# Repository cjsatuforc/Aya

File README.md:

# Aya

A general purpose TX module.

See `docs` for details/build instructions.

## Credits

  - [Deviation](http://www.deviationtx.com/) firmware

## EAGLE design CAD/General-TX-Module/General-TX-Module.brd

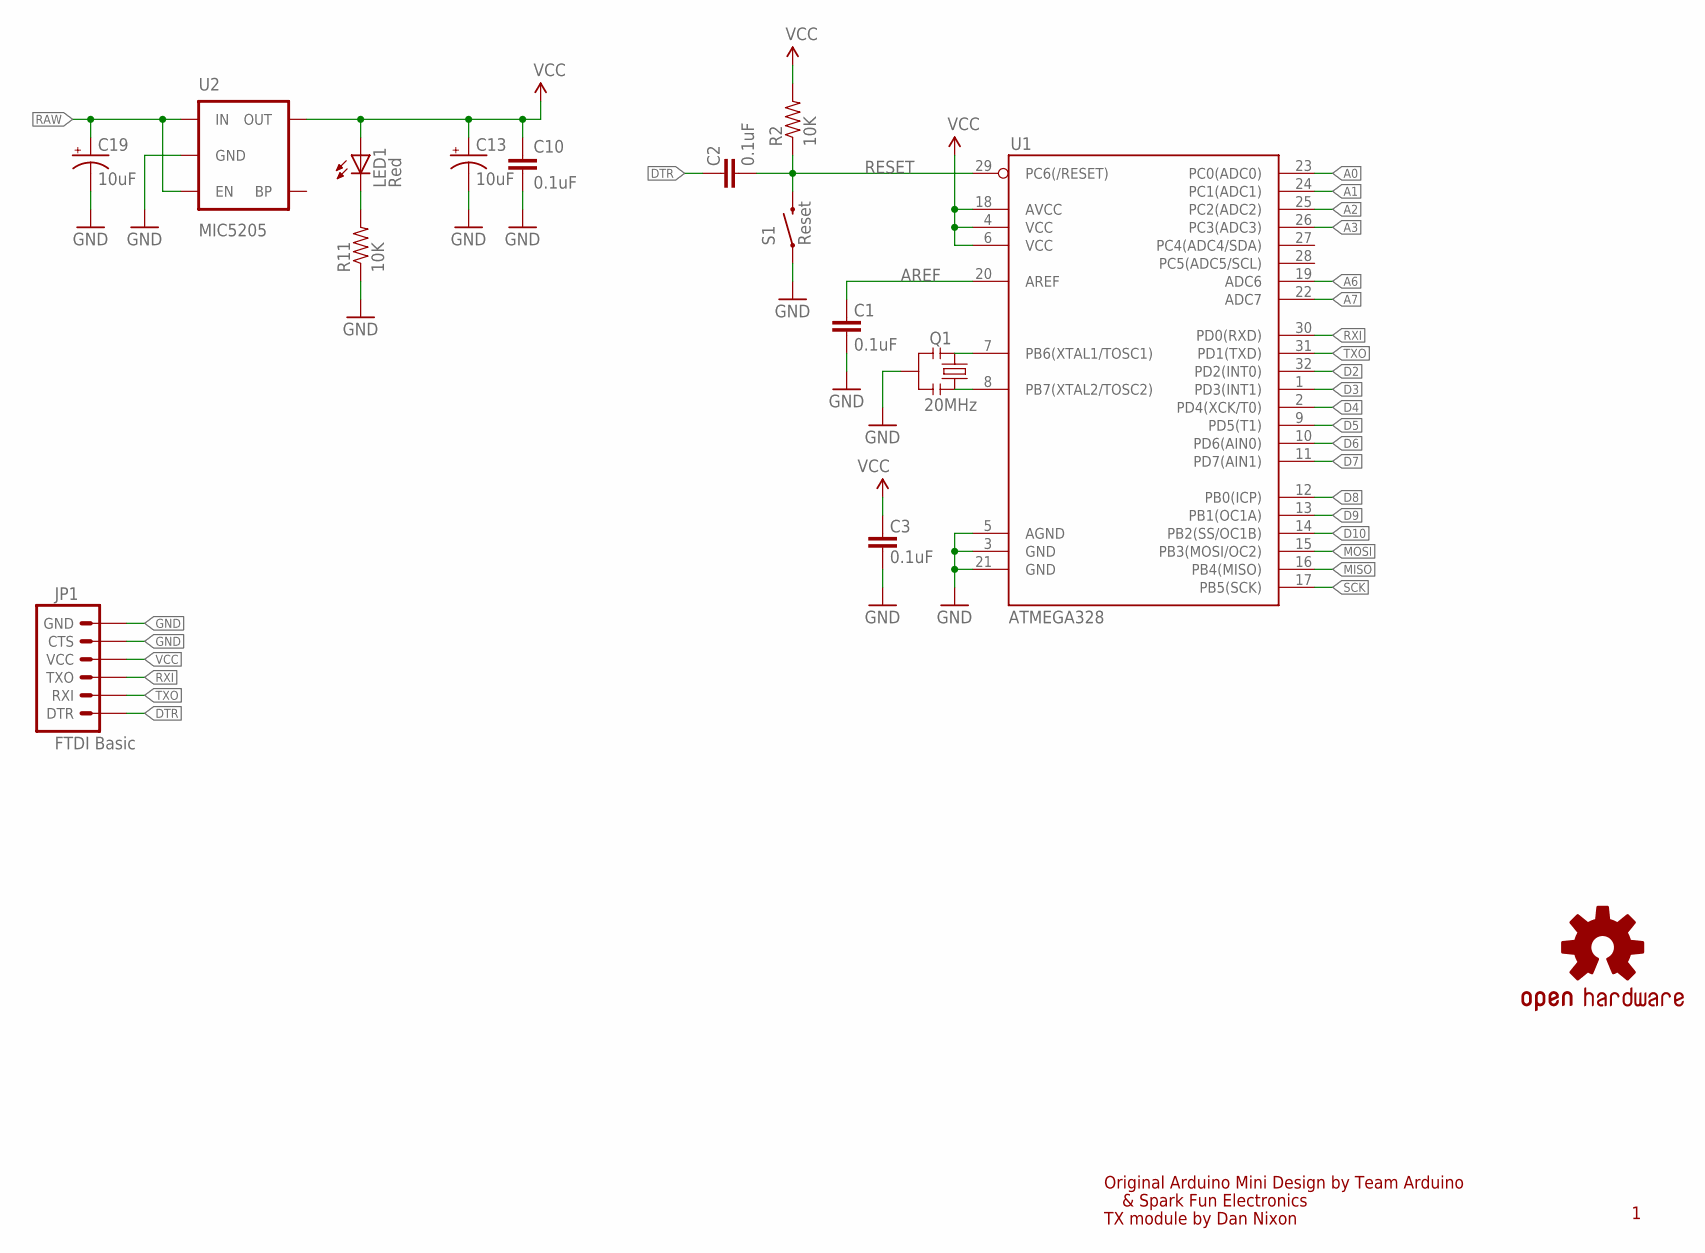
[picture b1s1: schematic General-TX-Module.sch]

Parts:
C1, C2, C3, C10: 0.1uF; 0603-CAP
C13, C19: 10uF; EIA3216
JP1: FTDI Basic; 1X06
LED1: Red; 0603-LED-ALT1
Q1: 20MHz; RESONATOR-SMD-1:1
R2, R11: 10K; 0603-RES
S1: Reset; TACTILE-SWITCH-SMD-ALT01
U1: ATMEGA328; TQFP32-08
U2: MIC5205; SOT23-5
U$3: OSHW-LOGOS; OSHW-LOGO-S

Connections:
A0: U1.23 (PC0(ADC0))
A1: U1.24 (PC1(ADC1))
A2: U1.25 (PC2(ADC2))
A3: U1.26 (PC3(ADC3))
A6: U1.19 (ADC6)
A7: U1.22 (ADC7)
AREF: C1.2, U1.20 (AREF)
D2: U1.32 (PD2(INT0))
D3: U1.1 (PD3(INT1))
D4: U1.2 (PD4(XCK/T0))
D5: U1.9 (PD5(T1))
D6: U1.10 (PD6(AIN0))
D7: U1.11 (PD7(AIN1))
D8: U1.12 (PB0(ICP))
D9: U1.13 (PB1(OC1A))
D10: U1.14 (PB2(SS/OC1B))
DTR: C2.2, JP1.1 (DTR)
GND: C1.1, C3.1, C10.2, C13.C (-), C19.C (-), JP1.5 (CTS), JP1.6 (GND), Q1.2, R11.1, S1.1, S1.2 (1), U1.3 (GND), U1.5 (AGND), U1.21 (GND), U2.2 (GND)
MISO: U1.16 (PB4(MISO))
MOSI: U1.15 (PB3(MOSI/OC2))
unnamed: Q1.3, U1.8 (PB7(XTAL2/TOSC2))
unnamed: Q1.1, U1.7 (PB6(XTAL1/TOSC1))
unnamed: LED1.C, R11.2
RAW: C19.A (+), U2.1 (IN), U2.3 (EN)
RESET: C2.1, R2.1, S1.3 (2), S1.4 (2), U1.29 (PC6(/RESET))
RXI: JP1.3 (TXO), U1.30 (PD0(RXD))
SCK: U1.17 (PB5(SCK))
TXO: JP1.2 (RXI), U1.31 (PD1(TXD))
VCC: C3.2, C10.1, C13.A (+), JP1.4 (VCC), LED1.A, R2.2, U1.4 (VCC), U1.6 (VCC), U1.18 (AVCC), U2.5 (OUT)

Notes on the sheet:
Original Arduino Mini Design by Team Arduino
& Spark Fun Electronics
TX module by Dan Nixon

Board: 2 copper layers, 15 parts (2 on the bottom side), 11 nets, no tracks yet.

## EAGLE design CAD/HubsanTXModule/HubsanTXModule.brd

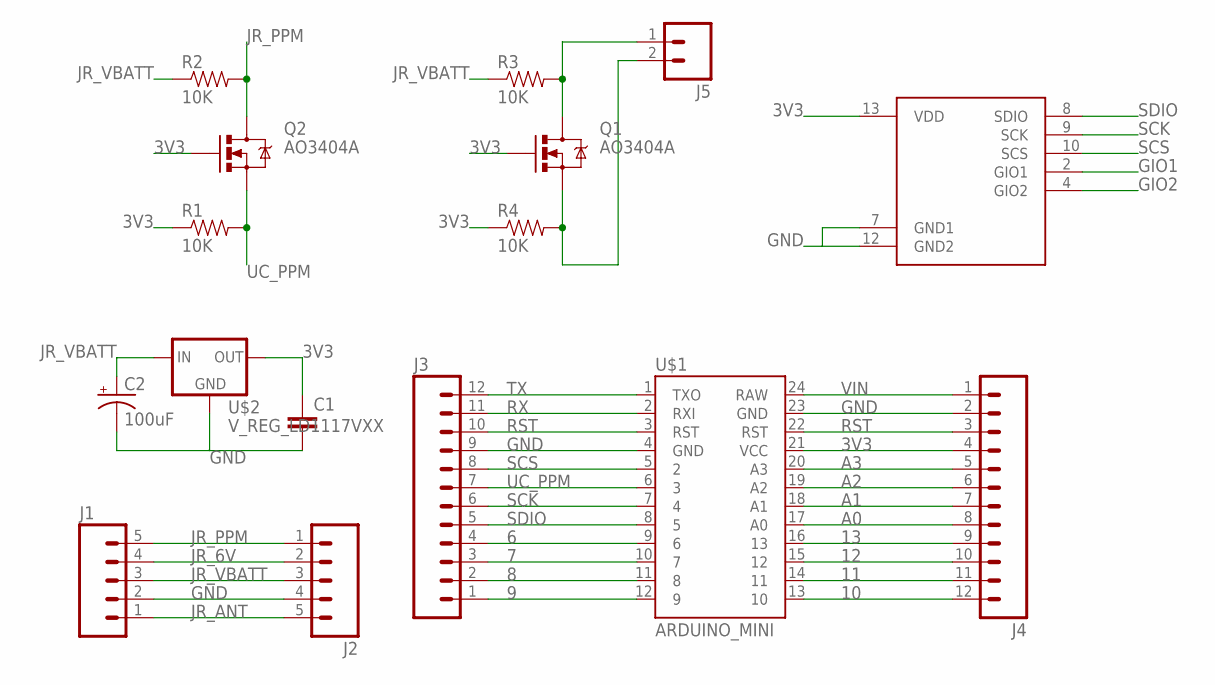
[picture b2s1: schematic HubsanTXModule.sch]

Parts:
C1: 10UF10V10%(0805); 0805-CAP
C2: 100uF; NIC_10X10.5_CAP
J1, J2: M05PTH; 1X05
J3, J4: M12PTH; 1X12
J5: M02PTH; 1X02
Q1, Q2: AO3404A; SOT23-3
R1, R2, R3, R4: 10K; 0603-RES
U$1: ARDUINO_MINI
U$2: V_REG_LD1117VXX; 78XXL
U$3: A7105_DEVBOARD; A7105_DEV1

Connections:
3V3: C1.1, J4.4, Q1.1 (G), Q2.1 (G), R1.1, R4.1, U$1.21 (VCC), U$2.GND (OUT), U$3.13 (VDD)
6: J3.4, U$1.9 (6)
7: J3.3, U$1.10 (7)
8: J3.2, U$1.11 (8)
9: J3.1, U$1.12 (9)
10: J4.12, U$1.13 (10)
11: J4.11, U$1.14 (11)
12: J4.10, U$1.15 (12)
13: J4.9, U$1.16 (13)
A0: J4.8, U$1.17 (A0)
A1: J4.7, U$1.18 (A1)
A2: J4.6, U$1.19 (A2)
A3: J4.5, U$1.20 (A3)
GIO1: U$3.2 (GIO1)
GIO2: U$3.4 (GIO2)
GND: C1.2, C2.-, J1.2, J2.4, J3.9, J4.2, U$1.4 (GND), U$1.23 (GND), U$2.IN (GND), U$3.7 (GND1), U$3.12 (GND2)
JR_6V: J1.4, J2.2
JR_ANT: J1.1, J2.5
JR_PPM: J1.5, J2.1, Q2.3 (D), R2.2
JR_VBATT: C2.+, J1.3, J2.3, R2.1, R3.1, U$2.OUT (IN)
unnamed: J5.2, Q1.2 (S), R4.2
unnamed: J5.1, Q1.3 (D), R3.2
RST: J3.10, J4.3, U$1.3 (RST), U$1.22 (RST)
RX: J3.11, U$1.2 (RXI)
SCK: J3.6, U$1.7 (4), U$3.9 (SCK)
SCS: J3.8, U$1.5 (2), U$3.10 (SCS)
SDIO: J3.5, U$1.8 (5), U$3.8 (SDIO)
TX: J3.12, U$1.1 (TXO)
UC_PPM: J3.7, Q2.2 (S), R1.2, U$1.6 (3)
VIN: J4.1, U$1.24 (RAW)

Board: 2 copper layers, 16 parts (0 on the bottom side), 28 nets, no tracks yet.

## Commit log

2016-01-08 CPPM code
2016-01-10 Add clang format
2016-01-12 Set pulse polarity
2016-01-20 Get working
2016-01-20 Make library, tidy
2016-01-20 Docs and performance tuning
2016-01-21 CLang format
    [ci skip]
2016-02-01 initial hubsan protocol
2016-02-01 comments, fix ranges
2016-02-01 small fixes
2016-02-01 clean
2016-02-01 wait for suitable conditions before binding
2016-02-01 build status badge
    [ci skip]
2016-02-01 Remove serial
2016-02-01 Fix flips
2016-02-01 Force binding if need be
2016-02-02 Add CAD stuff and simulator test
    [ci skip]
2016-02-11 Initial eagle files
2016-02-11 name nets for RF
2016-02-22 Fixes #1
2016-02-22 remove old files
2016-02-22 docs
2016-02-24 more work on board
2016-03-22 update docs
2016-03-22 reword
    [ci skip]
2016-03-31 start adding gener module
    Based on Arduino Pro Mini ref

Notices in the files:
parts and their libraries:
SparkFun-Boards: Licensing: Creative Commons ShareAlike 4.0 International - https://creativecommons.org/licenses/by-sa/4.0
